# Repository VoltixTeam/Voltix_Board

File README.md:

# Voltix Board Hardware Design Files

The Voltix board is a development board for battery-free wireless devices. The on-board wireless microcontroller runs off energy harvested from, for example, a solar panel and uses only tiny capacitors as energy storage. For uploading new software, the board can be connected to a PC via USB. During sotware upload and debugging, the microcontroller is powered with a fixed supply voltage from USB. After programming, the board automatically switches over to untethered, battery-free operation.

Latest design files:
 - [Schematics](https://voltix-docs.vercel.app/artifacts/board/latest/schematics.pdf)
 - [Layout](https://voltix-docs.vercel.app/artifacts/board/latest/pcb.pdf)
 - [Assembly plan](https://voltix-docs.vercel.app/artifacts/board/latest/assembly.pdf)
 - [3D rendering](https://voltix-docs.vercel.app/artifacts/board/latest/3drendering.png)

## Specification

Essentially, the Voltix board combines a [Voltix probe](https://github.com/VoltixTeam/Voltix_ProbeHardware) and a Voltix module on a single board. The board has two 0.1" pin sockets that expose all relevant signals from the battery-free device, including 10 GPIOs that can be flexibly used for I2C, SPI or for reading analog sensors. These headers are also used to connect voltix shields to build fully featured devices without having to design custom PCBs. The board comes with a push button, an LED and a connector for a solar panel.

Specification:
 - 56mm x 23mm board with two expansion headers for shields
 - Boost converter with software-defined maximum power point tracking and energy measurement
 - 66uF on-board capacitance
 - 2V regulated output voltage
 - 64 MHz ARM Cortex-M4 MCU with integrated 2.4GHz radio
 - 128kB non-volatile FRAM to retain appliccation state across power outages
 - Ultra-low power RTC with power management functionality
 - Capacitor voltage sensing and ultra low power comparator with software-controlled thresholds
 - USB-C connector
 - CMSIS-DAP compatible: Supports programming via pyOCD and OpenOCD
 - Makes UART output from battery-free device available via USB
 - Push button and User LED

## Firmware

The board has a dedicated controller (Raspberry Pi RP2040) that manages the upload of new firmware and the communication with a PC. This controller is powered from USB whenever the board is connected to a PC. The software running on the controller is the same as on the [Voltix probe](https://github.com/VoltixTeam/Voltix_ProbeHardware) and can be found in [this repository](https://github.com/VoltixTeam/Voltix_ProbeSoftware). To upgrade the firmware on the controller, connect a wire from one of the ground pins to the test pad labelled 'USB_BOOT' on the bottom of the board, while plugging in the USB cable. A removable storage drive should appear on your PC. Drop a UF2 compatible binary into the drive.

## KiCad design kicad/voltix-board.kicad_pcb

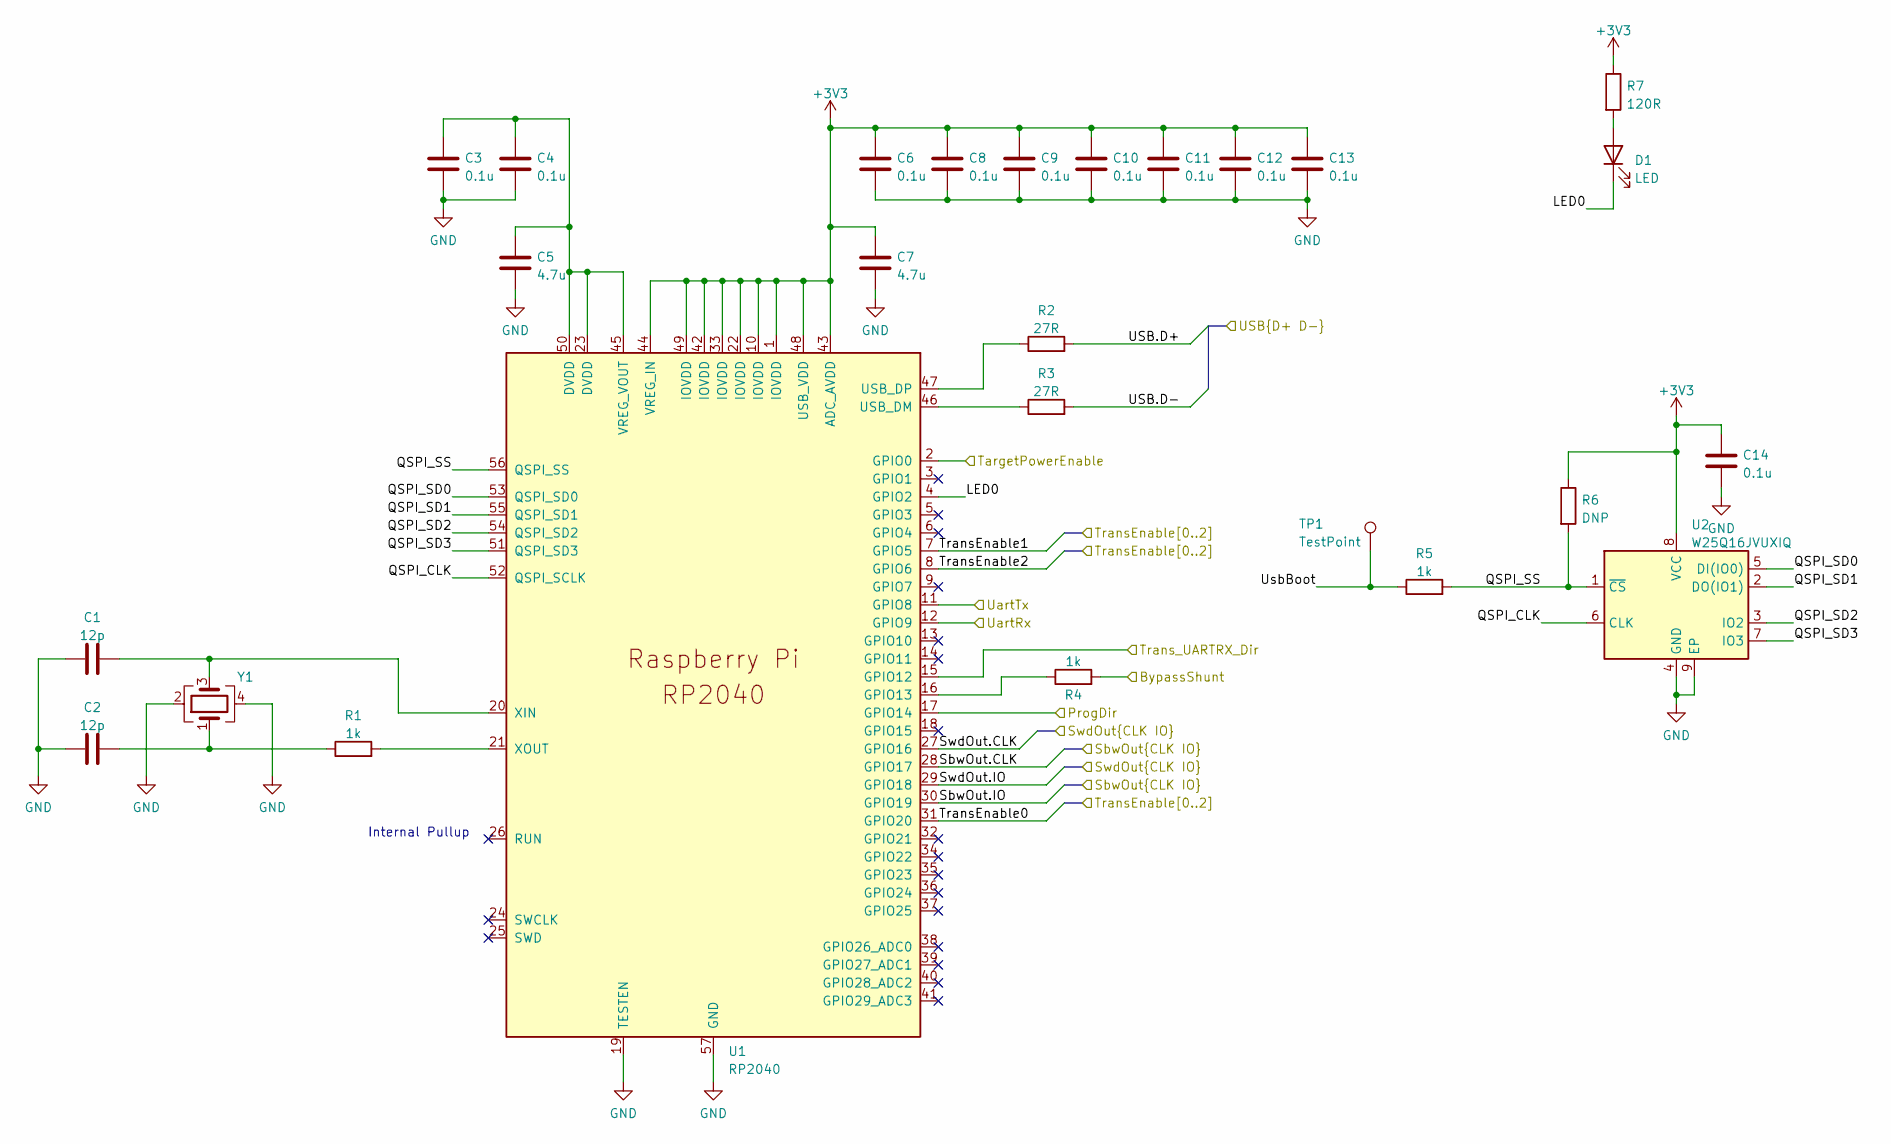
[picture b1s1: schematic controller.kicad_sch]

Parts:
C1, C2: 12p; C_0402_1005Metric; MPN 04025A120JAT2A
C3, C4, C6, C8, C9, C10, C11, C12, C13, C14: 0.1u; C_0402_1005Metric; MPN CL05A104KA5NNNC
C5, C7: 4.7u; C_0402_1005Metric; MPN CL05A475MP5NRNC
D1: LED; LED_0402_1005Metric; MPN QBLP595-AG1
R1, R4, R5: 1k; R_0402_1005Metric; MPN WR04X1001FTL
R2, R3: 27R; R_0402_1005Metric; MPN CR0402-FX-27R0GLF
R6: DNP; R_0402_1005Metric
R7: 120R; R_0402_1005Metric; MPN CR0402-FX-1200GLF
TP1: TestPoint; TestPoint_Pad_D1.0mm
U1: RP2040; RP_RP2040; MPN SC0914(13)
U2: W25Q16JVUXIQ; WB_UX8; MPN W25Q16JVUXIQ
Y1: Crystal_GND24; RALTRON_RH100; MPN RH100-12.000-18-2030-TR

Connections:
+3V3: C6.1, C7.1, C8.1, C9.1, C10.1, C11.1, C12.1, C13.1, C14.1, R6.1, R7.1, U1.1 (IOVDD), U1.10 (IOVDD), U1.22 (IOVDD), U1.33 (IOVDD), U1.42 (IOVDD), U1.43 (ADC_AVDD), U1.44 (VREG_IN), U1.48 (USB_VDD), U1.49 (IOVDD), U2.8 (VCC); also elsewhere on the board
/Controller/BypassShunt: R4.2; also elsewhere on the board
/Controller/LED0: D1.1 (K), U1.4 (GPIO2)
/Controller/ProgDir: U1.17 (GPIO14); also elsewhere on the board
/Controller/QSPI_CLK: U1.52 (QSPI_SCLK), U2.6 (CLK)
/Controller/QSPI_SD0: U1.53 (QSPI_SD0), U2.5 (DI(IO0))
/Controller/QSPI_SD1: U1.55 (QSPI_SD1), U2.2 (DO(IO1))
/Controller/QSPI_SD2: U1.54 (QSPI_SD2), U2.3 (IO2)
/Controller/QSPI_SD3: U1.51 (QSPI_SD3), U2.7 (IO3)
/Controller/QSPI_SS: R5.2, R6.2, U1.56 (QSPI_SS), U2.1 (~CS)
/Controller/SbwOut.CLK: U1.28 (GPIO17); also elsewhere on the board
/Controller/SbwOut.IO: U1.30 (GPIO19); also elsewhere on the board
/Controller/SwdOut.CLK: U1.27 (GPIO16); also elsewhere on the board
/Controller/SwdOut.IO: U1.29 (GPIO18); also elsewhere on the board
/Controller/TargetPowerEnable: U1.2 (GPIO0); also elsewhere on the board
/Controller/TransEnable0: U1.31 (GPIO20); also elsewhere on the board
/Controller/TransEnable1: U1.7 (GPIO5); also elsewhere on the board
/Controller/TransEnable2: U1.8 (GPIO6); also elsewhere on the board
/Controller/Trans_UARTRX_Dir: U1.15 (GPIO12); also elsewhere on the board
/Controller/USB.D+: R2.2; also elsewhere on the board
/Controller/USB.D-: R3.2; also elsewhere on the board
/Controller/UartRx: U1.12 (GPIO9); also elsewhere on the board
/Controller/UartTx: U1.11 (GPIO8); also elsewhere on the board
/Controller/UsbBoot: R5.1, TP1.1
GND: C1.1, C2.2, C3.2, C4.2, C5.2, C6.2, C7.2, C8.2, C9.2, C10.2, C11.2, C12.2, C13.2, C14.2, U1.19 (TESTEN), U1.57 (GND), U2.4 (GND), U2.9 (EP), Y1.2, Y1.4; also elsewhere on the board
unnamed: C2.1, R1.1, Y1.1
unnamed: D1.2 (A), R7.2
unnamed: R4.1, U1.16 (GPIO13)
unnamed: R3.1, U1.46 (USB_DM)
unnamed: R2.1, U1.47 (USB_DP)
unnamed: C3.1, C4.1, C5.1, U1.23 (DVDD), U1.45 (VREG_VOUT), U1.50 (DVDD)
unnamed: C1.2, U1.20 (XIN), Y1.3
unnamed: R1.2, U1.21 (XOUT)

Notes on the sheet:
Internal Pullup

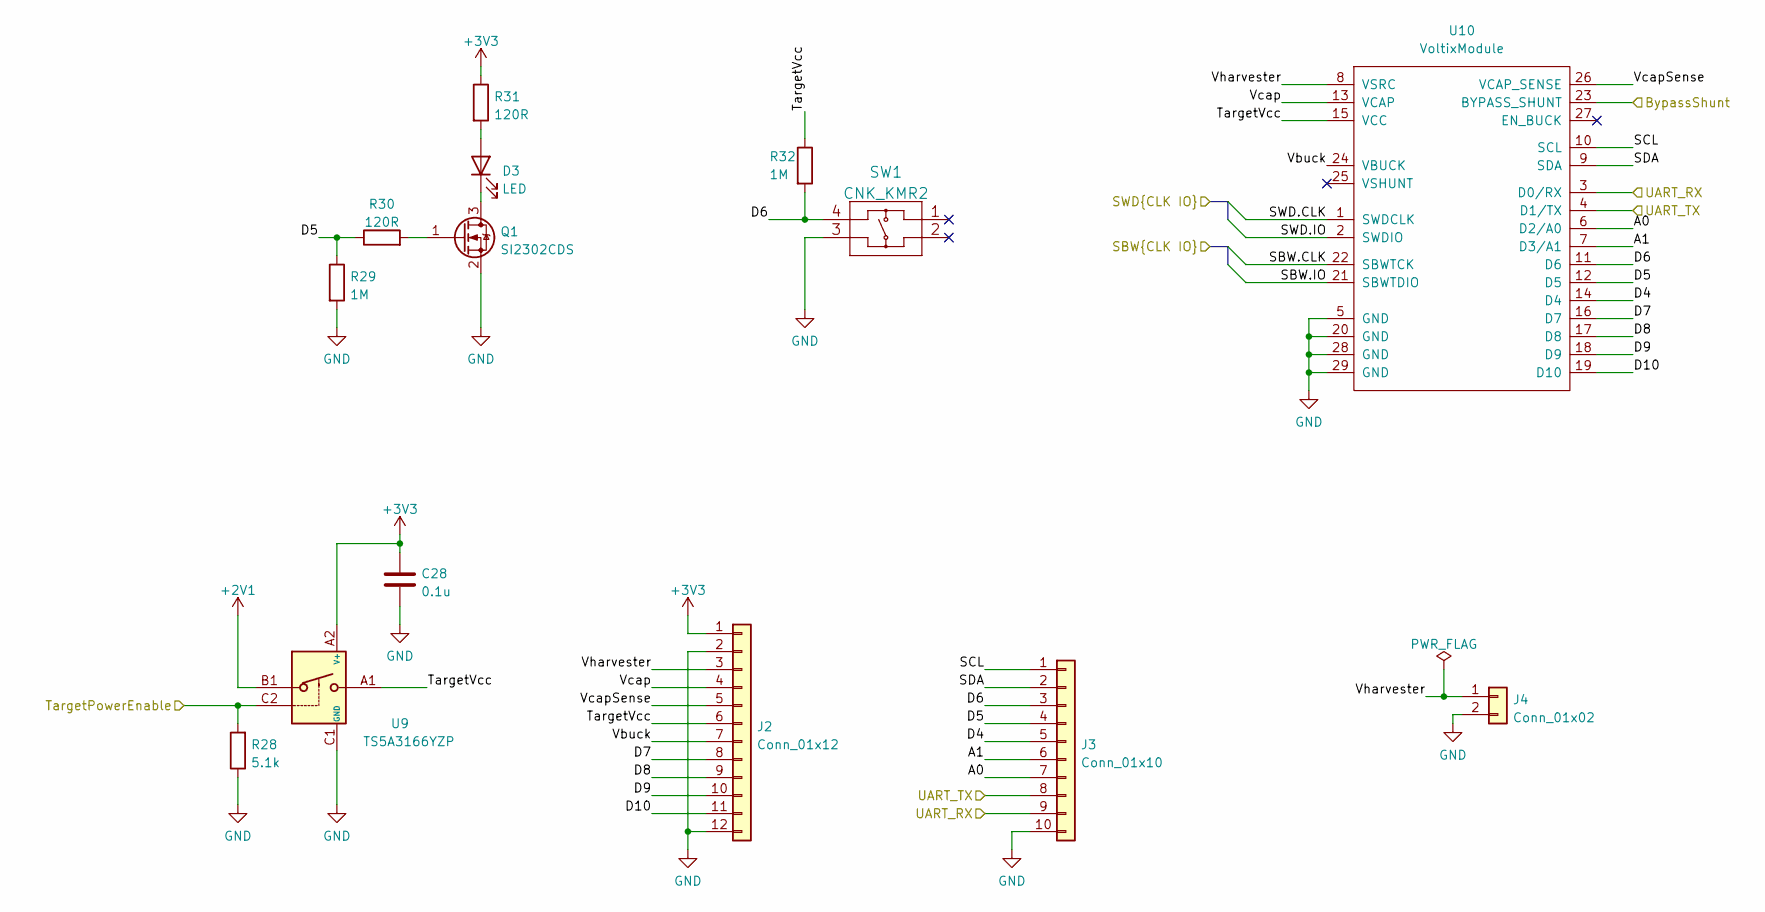
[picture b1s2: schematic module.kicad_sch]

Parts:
C28: 0.1u; C_0402_1005Metric; MPN CL05A104KA5NNNC
D3: LED; LED_0402_1005Metric; MPN QBLP595-AG1
J2: Conn_01x12; PinSocket_1x12_P2.54mm_Vertical; MPN PPPC121LFBN-RC
J3: Conn_01x10; PinSocket_1x10_P2.54mm_Vertical; MPN PPPC101LFBN-RC
J4: Conn_01x02; JST_S2B-PH-SM4-TB(LF)(SN); MPN 620102131822
Q1: SI2302CDS; VSH_SOT-23-3; MPN SI2302CDS-T1-GE3
R28: 5.1k; R_0402_1005Metric; MPN CR0402-FX-5101GLF
R29, R32: 1M; R_0402_1005Metric; MPN WR04X1004FTL
R30, R31: 120R; R_0402_1005Metric; MPN CR0402-FX-1200GLF
SW1: CNK_KMR2; CNK_KMR2_SW; MPN KMR221NG LFS
U9: TS5A3166YZP; TI_YZP0005; MPN TS5A3166YZP
U10: VoltixModule; NC_VoltixModule

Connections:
+2V1: U9.B1; also elsewhere on the board
+3V3: C28.1, J2.1, R31.1, U9.A2 (V+); also elsewhere on the board
/Controller/BypassShunt: U10.23 (BYPASS_SHUNT); also elsewhere on the board
/Controller/TargetPowerEnable: R28.2, U9.C2; also elsewhere on the board
/LevelShifter/Target_SBW.CLK: U10.22 (SBWTCK); also elsewhere on the board
/LevelShifter/Target_SBW.IO: U10.21 (SBWTDIO); also elsewhere on the board
/LevelShifter/Target_SWD.CLK: U10.1 (SWDCLK); also elsewhere on the board
/LevelShifter/Target_SWD.IO: U10.2 (SWDIO); also elsewhere on the board
/LevelShifter/Target_UART_RX: J3.9, U10.3 (D0/RX); also elsewhere on the board
/LevelShifter/Target_UART_TX: J3.8, U10.4 (D1/TX); also elsewhere on the board
/Voltix Module/A0: J3.7, U10.6 (D2/A0)
/Voltix Module/A1: J3.6, U10.7 (D3/A1)
/Voltix Module/D4: J3.5, U10.14 (D4)
/Voltix Module/D5: J3.4, R29.1, R30.1, U10.12 (D5)
/Voltix Module/D6: J3.3, R32.2, SW1.4, U10.11 (D6)
/Voltix Module/D7: J2.8, U10.16 (D7)
/Voltix Module/D8: J2.9, U10.17 (D8)
/Voltix Module/D9: J2.10, U10.18 (D9)
/Voltix Module/D10: J2.11, U10.19 (D10)
/Voltix Module/SCL: J3.1, U10.10 (SCL)
/Voltix Module/SDA: J3.2, U10.9 (SDA)
/Voltix Module/TargetVcc: J2.6, R32.1, U9.A1, U10.15 (VCC)
/Voltix Module/Vbuck: J2.7, U10.24 (VBUCK)
/Voltix Module/Vcap: J2.4, U10.13 (VCAP)
/Voltix Module/VcapSense: J2.5, U10.26 (VCAP_SENSE)
/Voltix Module/Vharvester: J2.3, J4.1, U10.8 (VSRC)
GND: C28.2, J2.2, J2.12, J3.10, J4.2, Q1.2 (S), R28.1, R29.2, SW1.3, U9.C1 (GND), U10.5 (GND), U10.20 (GND), U10.28 (GND), U10.29 (GND); also elsewhere on the board
unnamed: D3.2 (A), R31.2
unnamed: D3.1 (K), Q1.3 (D)
unnamed: Q1.1 (G), R30.2

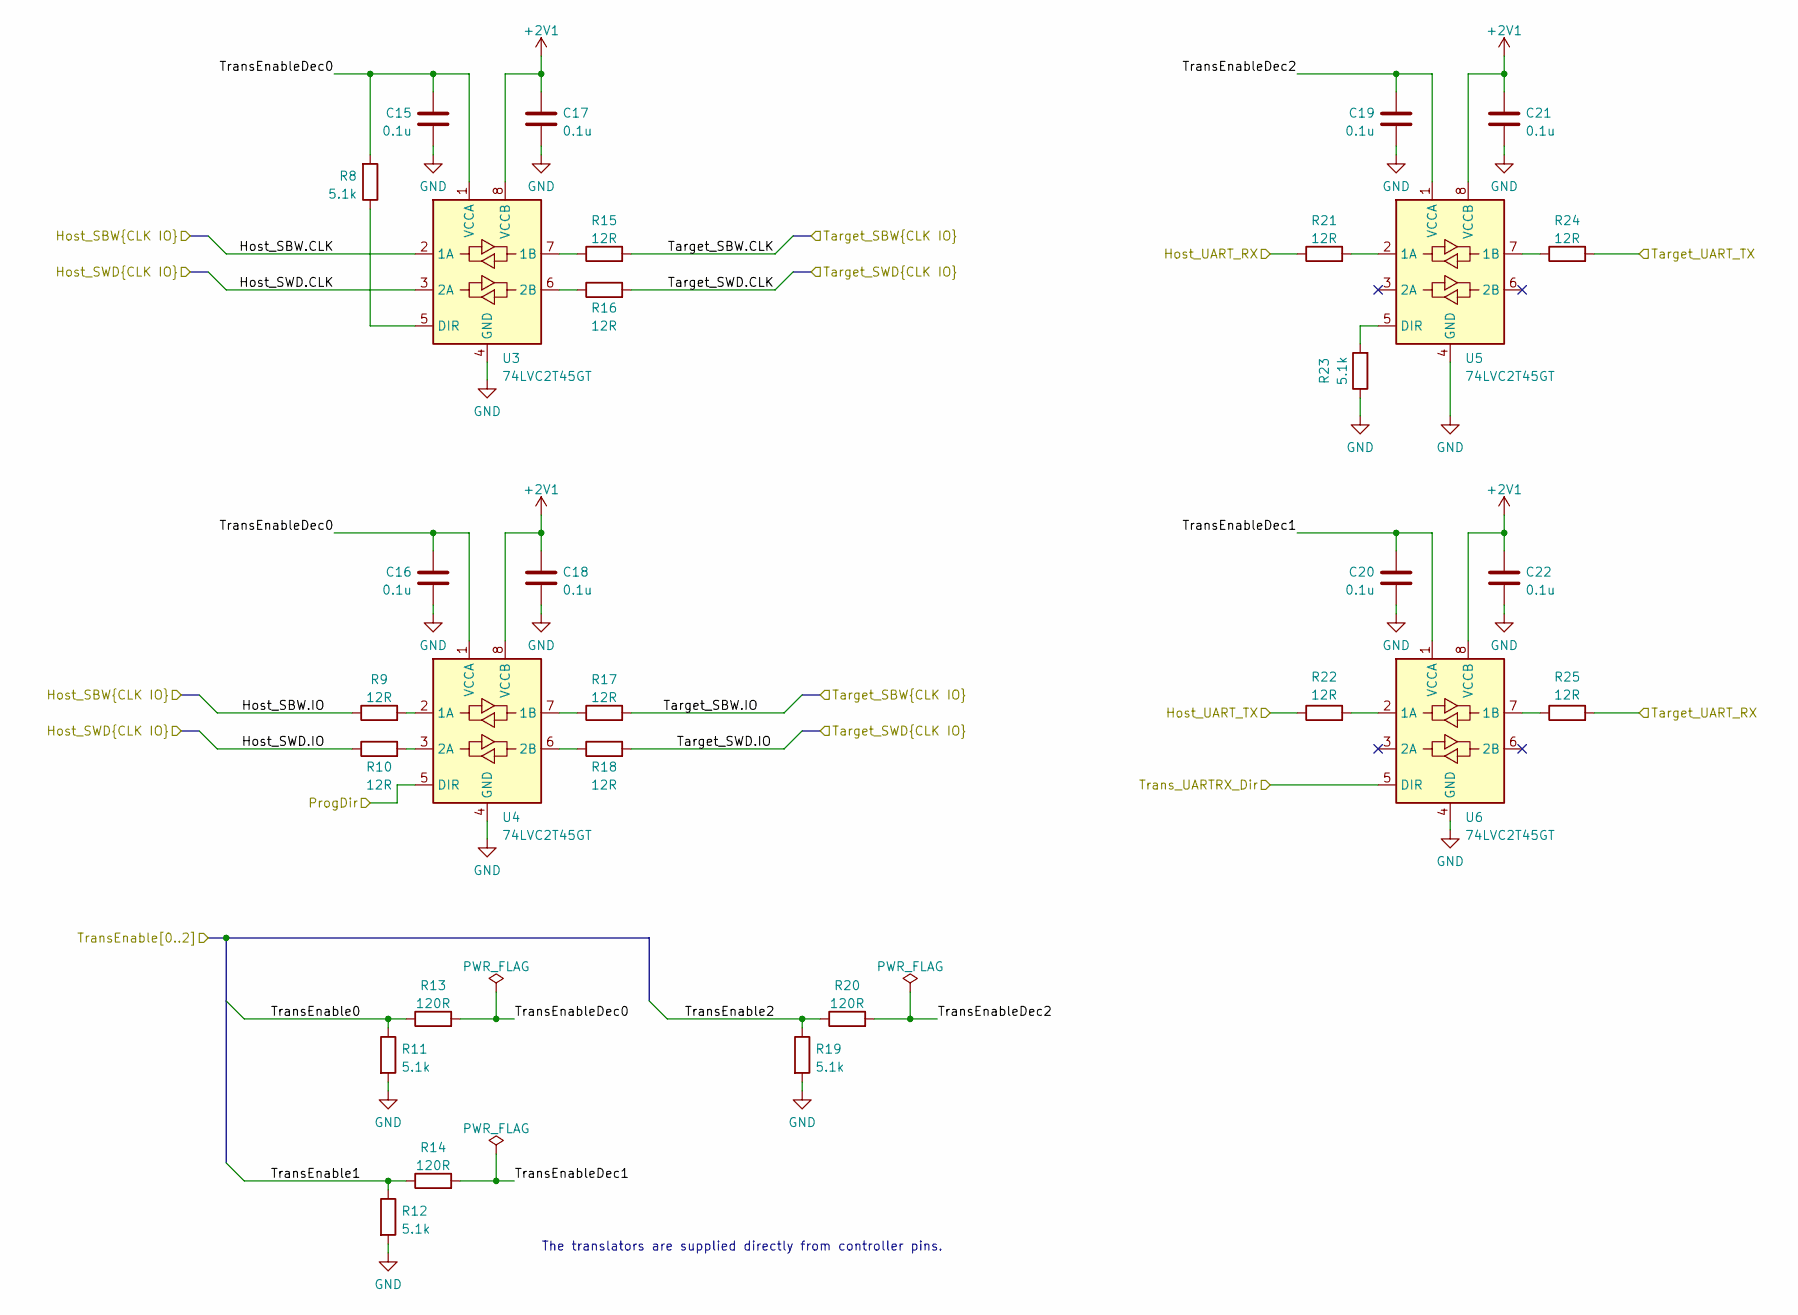
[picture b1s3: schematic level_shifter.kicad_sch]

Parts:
C15, C16, C17, C18, C19, C20, C21, C22: 0.1u; C_0402_1005Metric; MPN CL05A104KA5NNNC
R8, R11, R12, R19, R23: 5.1k; R_0402_1005Metric; MPN CR0402-FX-5101GLF
R9, R10, R15, R16, R17, R18, R21, R22, R24, R25: 12R; R_0402_1005Metric; MPN RMCF0402FT12R0
R13, R14, R20: 120R; R_0402_1005Metric; MPN CR0402-FX-1200GLF
U3, U4, U5, U6: 74LVC2T45GT; NXP_SOT833-1; MPN 74LVC2T45GT,115

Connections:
+2V1: C17.1, C18.1, C21.1, C22.1, U3.8 (VCCB), U4.8 (VCCB), U5.8 (VCCB), U6.8 (VCCB); also elsewhere on the board
/Controller/ProgDir: U4.5 (DIR); also elsewhere on the board
/Controller/SbwOut.CLK: U3.2 (1A); also elsewhere on the board
/Controller/SbwOut.IO: R9.1; also elsewhere on the board
/Controller/SwdOut.CLK: U3.3 (2A); also elsewhere on the board
/Controller/SwdOut.IO: R10.1; also elsewhere on the board
/Controller/TransEnable0: R11.1, R13.1; also elsewhere on the board
/Controller/TransEnable1: R12.1, R14.1; also elsewhere on the board
/Controller/TransEnable2: R19.1, R20.1; also elsewhere on the board
/Controller/Trans_UARTRX_Dir: U6.5 (DIR); also elsewhere on the board
/Controller/UartRx: R21.1; also elsewhere on the board
/Controller/UartTx: R22.1; also elsewhere on the board
/LevelShifter/Target_SBW.CLK: R15.2; also elsewhere on the board
/LevelShifter/Target_SBW.IO: R17.2; also elsewhere on the board
/LevelShifter/Target_SWD.CLK: R16.2; also elsewhere on the board
/LevelShifter/Target_SWD.IO: R18.2; also elsewhere on the board
/LevelShifter/Target_UART_RX: R25.2; also elsewhere on the board
/LevelShifter/Target_UART_TX: R24.2; also elsewhere on the board
/LevelShifter/TransEnableDec0: C15.2, C16.2, R8.2, R13.2, U3.1 (VCCA), U4.1 (VCCA)
/LevelShifter/TransEnableDec1: C20.2, R14.2, U6.1 (VCCA)
/LevelShifter/TransEnableDec2: C19.2, R20.2, U5.1 (VCCA)
GND: C15.1, C16.1, C17.2, C18.2, C19.1, C20.1, C21.2, C22.2, R11.2, R12.2, R19.2, R23.1, U3.4 (GND), U4.4 (GND), U5.4 (GND), U6.4 (GND); also elsewhere on the board
unnamed: R15.1, U3.7 (1B)
unnamed: R16.1, U3.6 (2B)
unnamed: R8.1, U3.5 (DIR)
unnamed: R9.2, U4.2 (1A)
unnamed: R17.1, U4.7 (1B)
unnamed: R10.2, U4.3 (2A)
unnamed: R18.1, U4.6 (2B)
unnamed: R21.2, U5.2 (1A)
unnamed: R24.1, U5.7 (1B)
unnamed: R23.2, U5.5 (DIR)
unnamed: R22.2, U6.2 (1A)
unnamed: R25.1, U6.7 (1B)

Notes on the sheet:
The translators are supplied directly from controller pins.

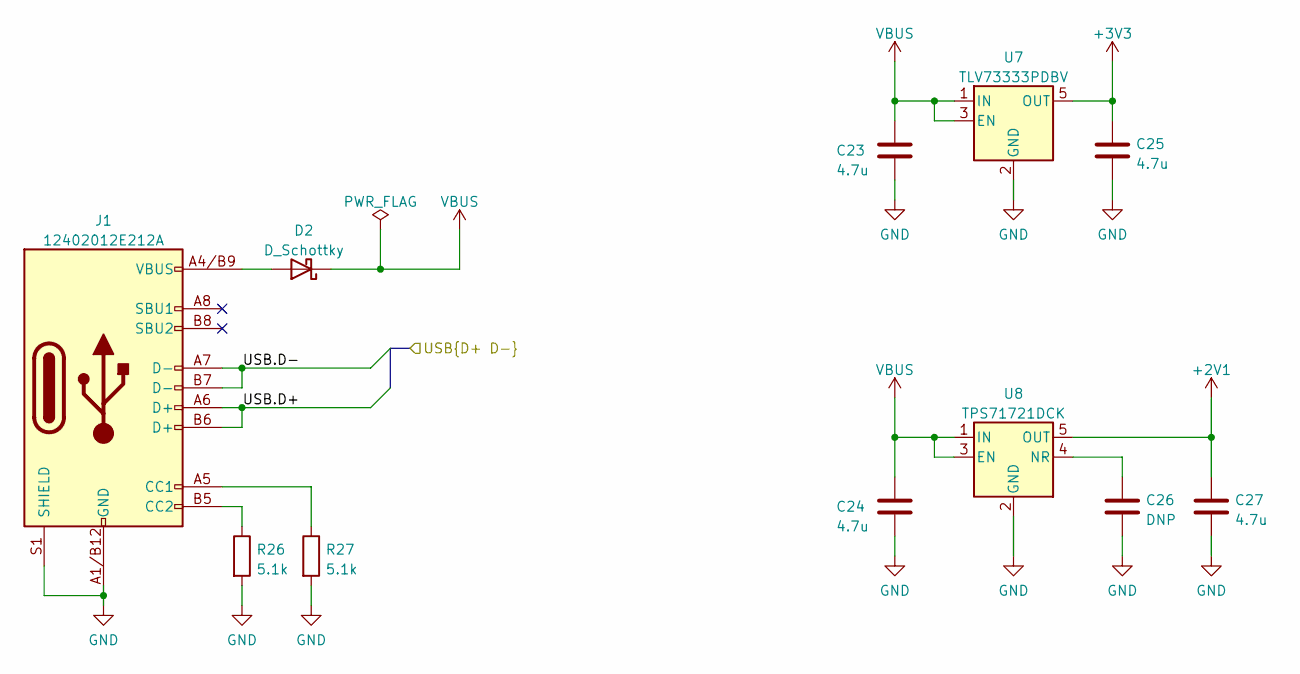
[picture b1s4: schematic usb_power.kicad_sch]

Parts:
C23, C24, C25, C27: 4.7u; C_0402_1005Metric; MPN CL05A475MP5NRNC
C26: DNP; C_0402_1005Metric
D2: D_Schottky; D_SOD-523; MPN RB521S30T1G
J1: 12402012E212A; AMPH_12402012E212A; MPN 12402012E212A
R26, R27: 5.1k; R_0402_1005Metric; MPN CR0402-FX-5101GLF
U7: TLV73333PDBV; TI_DBV0005A; MPN TLV73333PDBV
U8: TPS71721DCK; TI_DCK0005A; MPN TPS71721DCK

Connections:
+2V1: C27.1, U8.5 (OUT); also elsewhere on the board
+3V3: C25.1, U7.5 (OUT); also elsewhere on the board
/Controller/USB.D+: J1.A6 (D+), J1.B6 (D+); also elsewhere on the board
/Controller/USB.D-: J1.A7 (D-), J1.B7 (D-); also elsewhere on the board
GND: C23.2, C24.2, C25.2, C26.2, C27.2, J1.A1/B12 (GND), J1.B1/A12 (GND), J1.S1 (SHIELD), R26.2, R27.2, U7.2 (GND), U8.2 (GND); also elsewhere on the board
unnamed: D2.2 (A), J1.A4/B9 (VBUS), J1.B4/A9 (VBUS)
unnamed: J1.A5 (CC1), R27.1
unnamed: J1.B5 (CC2), R26.1
unnamed: C26.1, U8.4 (NR)
VBUS: C23.1, C24.1, D2.1 (K), U7.1 (IN), U7.3 (EN), U8.1 (IN), U8.3 (EN)

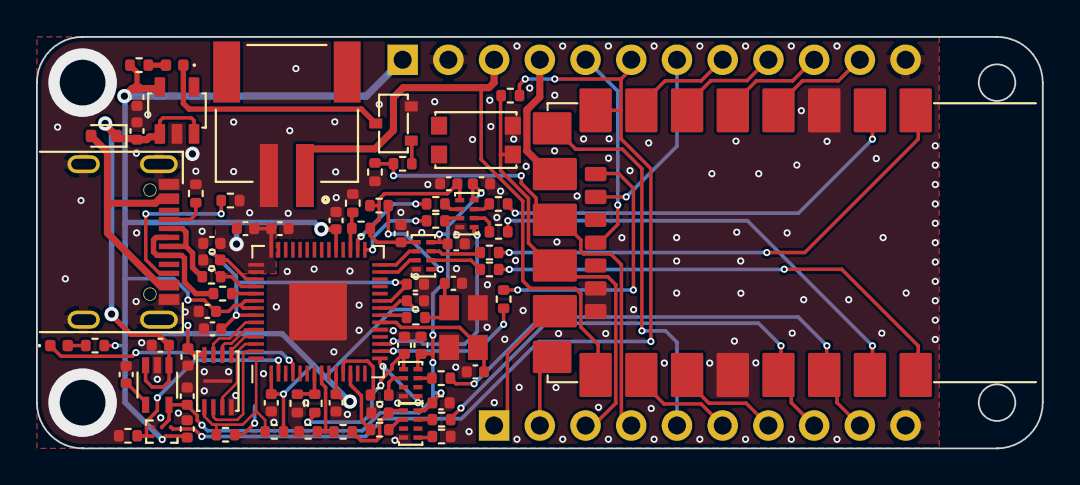
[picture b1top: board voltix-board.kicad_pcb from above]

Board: 4 copper layers, 55.9 x 22.9 mm, 81 parts (1 on the bottom side), 79 nets.

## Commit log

2024-06-26 add anonymized content
